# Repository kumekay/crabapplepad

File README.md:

# crabapplepad v2

Wireless minimalistic foldable split keyboard

## Features

- Supports Kailh Choc and MX switches
- Optionally foldable with Choc switches
- Minimalistic. No LEDs, no RGB, no extra keys
- With Kailh Choc it's 3cm thick in the folded state
- Split. The two halves are connected with a 3d printed hinge
- Wireless. Uses Nice!Nano or ProMicro nRF52840 with BLE
- 42 keys (I use Cyrillic layout too and 36 keys is not enough)
- Apple Magic Trackpad can be magnetically attached (optional)

## PCB design

PCB is generated using [ergogen](https://github.com/ergogen/ergogen). Then it finished in KiCAD.
To regenerate the PCB run:

```bash
npx ergogen . --clean && open output/pcbs/kbd.kicad_pcb
```

NB! The final PCB was heavily modified in KiCAD

## Firmware

The firmware is based on [ZMK](https://zmkfirmware.dev/) and [Myrioku Layout](https://github.com/manna-harbour/miryoku) adapted for 42 keys. T

## Where is the slim V1?

It's in the [v1](https://github.com/kumekay/crabapplepad/tree/v1) branch. The V1 is ccm thick in the folded state with Kailh X switches. The V2 is 3cm thick with Kailh Choc switches.

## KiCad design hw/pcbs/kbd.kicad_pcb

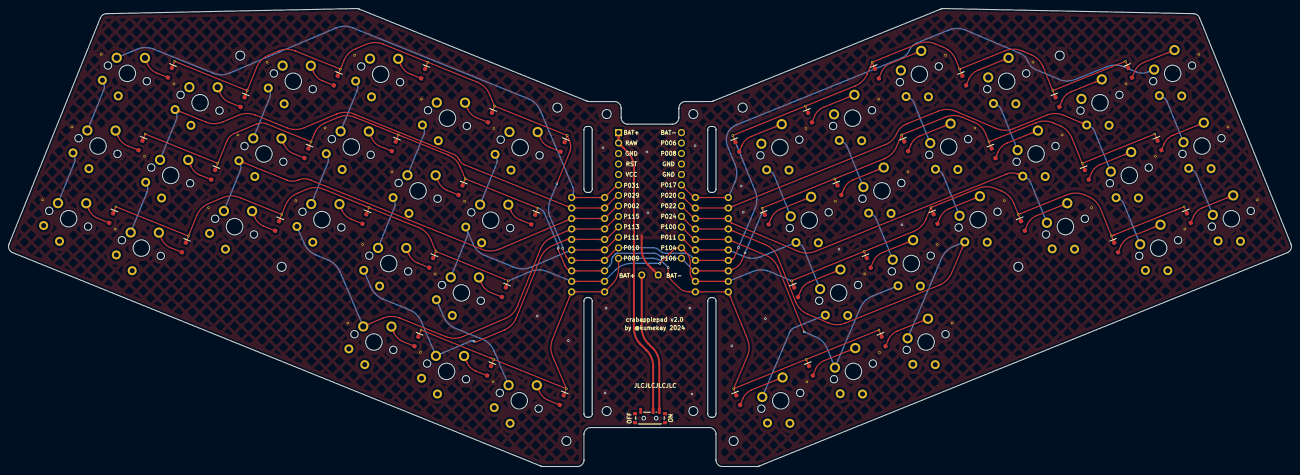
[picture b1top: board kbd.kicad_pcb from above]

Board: 2 copper layers, 311.0 x 111.0 mm, 98 parts (0 on the bottom side), 60 nets.

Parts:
D1, D2, D3, D4, D5, D6, D7, D8, D9, D10, D11, D12, D13, D14, D15, D16, D17, D18, D19, D20, D21, D22, D23, D24, D25, D26, D27, D28, D29, D30, D31, D32, D33, D34, D35, D36, D37, D38, D39, D40, D41, D42: D_SOD-323_HandSoldering
MCU1: ProMicro
PWR1: power_switch_smd_side
S1, S2, S3, S4, S5, S6, S7, S8, S9, S10, S11, S12, S13, S14, S15, S16, S17, S18, S19, S20, S21, S22, S23, S24, S25, S26, S27, S28, S29, S30, S31, S32, S33, S34, S35, S36, S37, S38, S39, S40, S41, S42: SW_MX_Choc_PCB_1.00u; SW_Cherry_MX_Choc_PCB_1.00u_nosilk
_129, _130, _131, _132, _133, _134, _135, _136, _137, _138, _139, _140: MountingHole_2.2mm_M2_DIN965

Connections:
GND: MCU1.3, MCU1.14, MCU1.17, MCU1.18
P002: MCU1.8, S7.1, S8.1, S9.1
P009: D19.1, D20.1, D21.1, D40.1, D41.1, D42.1, MCU1.13
P010: D3.1, D6.1, D9.1, D12.1, D15.1, D18.1, D24.1, D27.1, D30.1, D33.1, D36.1, D39.1, MCU1.12
P011: MCU1.24, S37.1, S38.1, S39.1, S42.1
P017: MCU1.19, S22.1, S23.1, S24.1
P020: MCU1.20, S25.1, S26.1, S27.1
P022: MCU1.21, S28.1, S29.1, S30.1
P024: MCU1.22, S31.1, S32.1, S33.1, S40.1
P029: MCU1.7, S4.1, S5.1, S6.1
P031: MCU1.6, S1.1, S2.1, S3.1
P100: MCU1.23, S34.1, S35.1, S36.1, S41.1
P104: D1.1, D4.1, D7.1, D10.1, D13.1, D16.1, D22.1, D25.1, D28.1, D31.1, D34.1, D37.1, MCU1.25
P106: D2.1, D5.1, D8.1, D11.1, D14.1, D17.1, D23.1, D26.1, D29.1, D32.1, D35.1, D38.1, MCU1.26
P111: MCU1.11, S16.1, S17.1, S18.1, S21.1
P113: MCU1.10, S13.1, S14.1, S15.1, S20.1
P115: MCU1.9, S10.1, S11.1, S12.1, S19.1
RAW: MCU1.1, MCU1.2, PWR1.2
alpha_cluster: D19.2, S19.2
beta_cluster: D20.2, S20.2
gamma_cluster: D21.2, S21.2
index_bottom: D13.2, S13.2
index_home: D14.2, S14.2
index_top: D15.2, S15.2
inner_bottom: D16.2, S16.2
inner_home: D17.2, S17.2
inner_top: D18.2, S18.2
middle_bottom: D10.2, S10.2
middle_home: D11.2, S11.2
middle_top: D12.2, S12.2
mirror_alpha_cluster: D40.2, S40.2
mirror_beta_cluster: D41.2, S41.2
mirror_gamma_cluster: D42.2, S42.2
mirror_index_bottom: D34.2, S34.2
mirror_index_home: D35.2, S35.2
mirror_index_top: D36.2, S36.2
mirror_inner_bottom: D37.2, S37.2
mirror_inner_home: D38.2, S38.2
mirror_inner_top: D39.2, S39.2
mirror_middle_bottom: D31.2, S31.2
mirror_middle_home: D32.2, S32.2
mirror_middle_top: D33.2, S33.2
mirror_outer_bottom: D22.2, S22.2
mirror_outer_home: D23.2, S23.2
mirror_outer_top: D24.2, S24.2
mirror_pinky_bottom: D25.2, S25.2
mirror_pinky_home: D26.2, S26.2
mirror_pinky_top: D27.2, S27.2
mirror_ring_bottom: D28.2, S28.2
mirror_ring_home: D29.2, S29.2
mirror_ring_top: D30.2, S30.2
outer_bottom: D1.2, S1.2
outer_home: D2.2, S2.2
outer_top: D3.2, S3.2
pinky_bottom: D4.2, S4.2
pinky_home: D5.2, S5.2
pinky_top: D6.2, S6.2
ring_bottom: D7.2, S7.2
ring_home: D8.2, S8.2
ring_top: D9.2, S9.2

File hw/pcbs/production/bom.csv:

Designator,Footprint,Quantity,Value,LCSC Part #
"_42, _41, _40, _39, _38, _37, _36, _35, _34, _33, _32, _31, _30, _29, _28, _27, _26, _25, _24, _23, _22, _21, _20, _19, _18, _17, _16, _15, _14, _13, _12, _11, _10, _9, _8, _7, _6, _5, _4, _3, _2, ",PAD-1.0922mm,42,,
"D1, D10, D11, D12, D13, D14, D15, D16, D17, D18, D19, D2, D20, D21, D22, D23, D24, D25, D26, D27, D28, D29, D3, D30, D31, D32, D33, D34, D35, D36, D37, D38, D39, D4, D40, D41, D42, D5, D6, D7, D8, D9",D_SOD-323_HandSoldering,42,,
MCU1,ProMicro,1,,
PWR1,power_switch_smd_side,1,,
"S1, S10, S11, S12, S13, S14, S15, S16, S17, S18, S19, S2, S20, S21, S22, S23, S24, S25, S26, S27, S28, S29, S3, S30, S31, S32, S33, S34, S35, S36, S37, S38, S39, S4, S40, S41, S42, S5, S6, S7, S8, S9",SW_Cherry_MX_Choc_PCB_1.00u,42,SW_MX_Choc_PCB_1.00u,
"_129, _130, _131, _132, _133, _134, _135, _136, _137, _138, _139, _140",Mount_Hole_2.2mm_Pad_Via,12,,

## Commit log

2023-05-05 Initial layout
2023-05-06 Add outline
2023-05-08 Add mount holes
2023-05-09 Add switch footprint
2023-05-15 Add diodes and MCU
2023-05-22 Add cutouts
2023-05-23 Add connections
2023-05-23 Separate signals
2023-05-27 Redo mounting holes
2023-05-29 change magnet position
2023-05-31 Update mounting holes
2023-05-31 Add pin labels
2023-05-31 Adjust sliding slot
2023-06-04 Update nets and join parts
2023-06-04 Add mouse bites
2023-06-04 Add the PCB
2023-10-02 Add case files and update README
2023-10-02 Add ergogen command to Readme
2024-06-22 feat: Draft of V2
2024-06-23 feat: connect pads in mx-choc layout
2024-06-23 feat: add diodes and pins
2024-06-25 feat: finish connections and outlines
2024-06-25 fix: mout holes
2024-06-27 feat: add power switch
2024-06-27 feat: add new kicad project
2024-06-29 feat: wip version of the board
2024-06-29 feat: v2 production files
2024-06-30 fix: Update production files
2024-07-01 docs: Update readme
2024-07-01 docs: add v1 link
2024-07-11 feat: add keyholder 3d model
2024-07-12 refactor: move out of hw keyboard
2024-07-12 feat: add mount holes to outlines
2024-07-20 feat: Add keyholder for choc
